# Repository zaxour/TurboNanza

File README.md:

# TurboNanza

***NOTE: I will provide support for Turbonanza if you purchased from:

My Ko-Fi Store: https://ko-fi.com/s/4d0de1c0ac
VideoGamePerfection (EU): https://videogameperfection.com/products/turbonanza-pcengine-turbografx/

If you purchased from AliExpress, I cannot provide support as it looks like they changed the design and did not publish the details.

***

[PC Engine Shuttle Installation Instructions](/images/shuttle/readme.md)

[PC Engine/Turbo Duo Installation Instructions](/images/duo/readme.md)

An internal RGB, S-Video, Composite video and Audio modification for the Turbografx 16, PCEngine and CoreGrafx. As of Revision C, support has been added for audio from the Turbo Everdrive Pro.

Design is KiCad format and all files necessary to open the design and have it fabricated are present within the archive.

Installation Method (WORK IN PROGRESS!!):

PINOUT (For reference/Non-Expansion-Port Installs):

## Step 1 - Remove the resistors for Luma, R-Y, B-Y, and Burst
### PC Engine & CoreGrafx

Remove resistors R134, R137, R138 and R156 

### TurboGrafx 16
Remove resistors R130-R132 and R134

### SuperGrafx
Remove resistors R164-167

## Step 2 - Disconnect CVBS pin from original circuit
### PC Engine & CoreGrafx
Remove resistor R145 (20 ohms)

### TurboGrafx 16
Remove resistor R127 (20 ohms)

### SuperGrafx
Remove resistor R147 

## Step 3 - Install TurboNanza
### PC Engine & CoreGrafx
Solder the TurboNanza over the expansion port pins as shown.

### TurboGrafx16
Solder the TurboNanza over the expansion port pins as shown.

### SuperGrafx
Prepare the flex cable by tinning the pads as shown.

Solder the TurboNanza to the flex cable as shown. It's recommended to verify continuity. Place some kapton/polyimide tape over the exposed solder pads on the bottom of the flex cable to avoid shorting to the shielding.

Solder the TurboNanza/Flex Cable combo over the expansion port pins as shown (ignore 4 wires at this time).

## Step 4 - Solder S-Video connections

**When soldering the Y/B-Y/R-Y/Burst wires, try to use as close to the exact same length of wire as possible to maintain proper phase shift!**

### PC Engine & CoreGrafx
Solder wires from the points shown to the pads on TurboNanza
(Do not remove R141, as previously directed. The Color Burst trace runs underneath and can easily sever. Leave R141 on and solder directly to the resistor pad)

### TurboGrafx 16
Solder wires from the points shown to the pads on TurboNanza

### SuperGrafx
Solder wires from the points shown to the pads on TurboNanza

## Step 5 - Attach the DIN to the main board
### PC Engine
Kits sold after 8/15/2023 now include a mounting board for the PCEngine. It is recommended to secure with two size M2 or 2-56 bolts/washers to allow for easy positioning.

Position the mount and loosely secure with screws/washers. The board may also be soldered - kapton/polyimide tape is recommended to position the board.

Place the DIN in the slot, and solder around the sides.

Solder the DIN FFC adapter to the DIN. Please make sure the "THIS SIDE TOP" text is visible before soldering, as it indicates which side is top.

### CoreGrafx
First, remove C162 (AC coupling capacitor for composite video - no longer necessary)

Scrape the solder mask off the copper on the left and right edges of the original DIN footprint as shown.

Solder the supplied mounting board to the mainboard.

Solder the DIN FFC adapter to the DIN. Please make sure the "THIS SIDE TOP" text is visible before soldering, as it indicates which side is top.

### TurboGrafx16
Solder the mounting board using the plated through holes for the RF modulator. Align the DIN on the mounting board such that it aligns with the console shell opening and solder in place.

### SuperGrafx
Remove the original DIN and scrape the soldermask approximately as shown.

Solder the mounting board as shown, aligning the center hole with the two ground through holes.

Mount the DIN and DIN board to the mount board.

## Step 6 - RF Shielding and Case trimming
### PC Engine
On the bottom shell of the case, trim the 2 ribs where the expansion port opening sits. Do not re-install the original shielding. If your PC Engine has shielding that has two tabs that solder close to the EXP port pins, you will need to run a wire to where the shielding originally terminated.

### CoreGrafx
Trim the RF shield such that the metal lip is not contacting the TurboNanza.

Like the PC Engine, trim the 2 ribs on the bottom shell where the expansion port opening is.

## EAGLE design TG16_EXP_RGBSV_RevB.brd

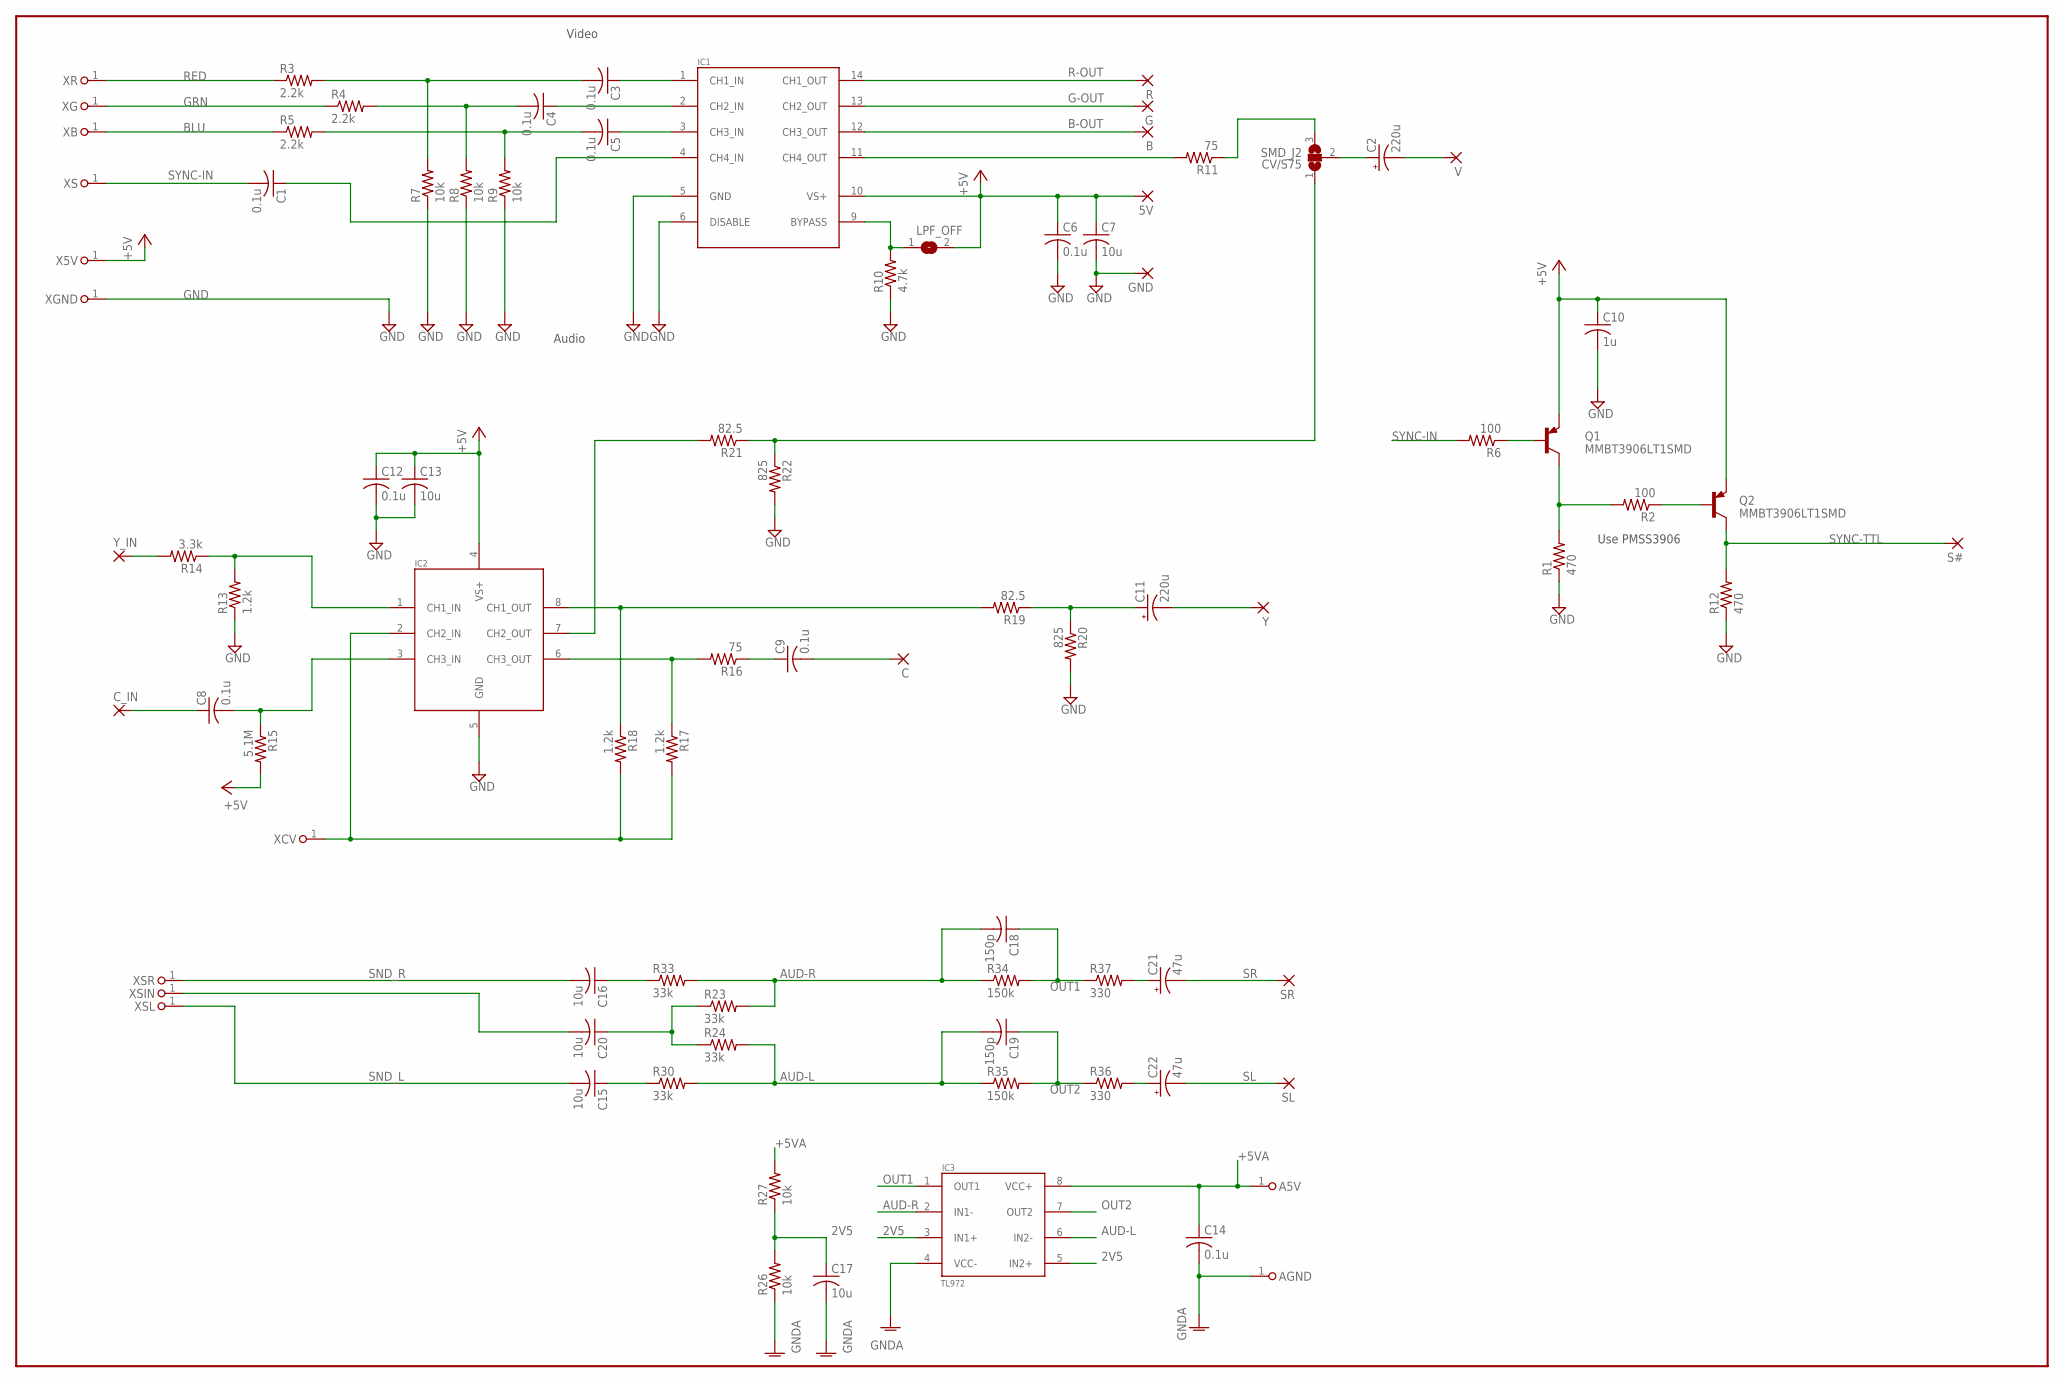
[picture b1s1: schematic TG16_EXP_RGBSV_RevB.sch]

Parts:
5V: SMD2; SMD1,27-2,54
A5V: PINHD-1X1; 1X01
AGND: PINHD-1X1; 1X01
B: SMD2; SMD1,27-2,54
C: SMD2; SMD1,27-2,54
C1, C3, C4, C5, C6, C8, C9, C12, C14: 0.1u; C0603
C2, C11: 220u; CT3528
C7, C13, C17: 10u; C1206
C10: 1u; C0603
C15, C16, C20: 10u; C0805
C18, C19: 150p; C0603
C21, C22: 47u; CT3528
CV/S75: SMD_J2; SJ_2
C_IN: SMD2; SMD1,27-2,54
G: SMD2; SMD1,27-2,54
GND: SMD2; SMD1,27-2,54
IC1: THS7374TSSOP14_LONG; TSSOP14LONG
IC2: THS7314; SOIC8
IC3: TL972; SOIC8
LPF_OFF: SMD_J; SJ
Q1, Q2: MMBT3906LT1SMD; SOT23-BEC
R: SMD2; SMD1,27-2,54
R1, R12: 470; R0603
R2, R6: 100; R0603
R3, R4, R5: 2.2k; R0603
R7, R8, R9, R26, R27: 10k; R0603
R10: 4.7k; R0603
R11, R16: 75; R0603
R13, R17, R18: 1.2k; R0603
R14: 3.3k; R0603
R15: 5.1M; R0603
R19, R21: 82.5; R0603
R20, R22: 825; R0603
R23, R24, R30, R33: 33k; R0603
R34, R35: 150k; R0603
R36, R37: 330; R0603
S#: SMD2; SMD1,27-2,54
SL: SMD2; SMD1,27-2,54
SR: SMD2; SMD1,27-2,54
V: SMD2; SMD1,27-2,54
X5V: PINHD-1X1; 1X01
XB: PINHD-1X1; 1X01
XCV: PINHD-1X1; 1X01
XG: PINHD-1X1; 1X01
XGND: PINHD-1X1; 1X01
XR: PINHD-1X1; 1X01
XS: PINHD-1X1; 1X01
XSIN: PINHD-1X1; 1X01
XSL: PINHD-1X1; 1X01
XSR: PINHD-1X1; 1X01
Y: SMD2; SMD1,27-2,54
Y_IN: SMD2; SMD1,27-2,54

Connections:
2V5: C17.1, IC3.3 (IN1+), IC3.5 (IN2+), R26.2, R27.1
+5V: 5V.1, C6.1, C7.1, C10.1, C12.1, C13.1, IC1.10 (VS+), IC2.4 (VS+), LPF_OFF.2, Q1.E, Q2.E, R15.2, X5V.1
+5VA: A5V.1, C14.1, IC3.8 (VCC+), R27.2
AUD-L: C19.2, IC3.6 (IN2-), R24.2, R30.2, R35.1
AUD-R: C18.2, IC3.2 (IN1-), R23.2, R33.2, R34.1
B-OUT: B.1, IC1.12 (CH3_OUT)
BLU: R5.1, XB.1
G-OUT: G.1, IC1.13 (CH2_OUT)
GND: C6.2, C7.2, C10.2, C12.2, C13.2, GND.1, IC1.5 (GND), IC1.6 (DISABLE), IC2.5 (GND), R1.1, R7.1, R8.1, R9.1, R10.1, R12.1, R13.1, R20.2, R22.2, XGND.1
GNDA: AGND.1, C14.2, C17.2, IC3.4 (VCC-), R26.1
GRN: R4.1, XG.1
unnamed: Q1.B, R6.1
unnamed: C3.1, IC1.1 (CH1_IN)
unnamed: C3.2, R3.2, R7.2
unnamed: C4.1, IC1.2 (CH2_IN)
unnamed: C4.2, R4.2, R8.2
unnamed: C5.1, IC1.3 (CH3_IN)
unnamed: C1.1, IC1.4 (CH4_IN)
unnamed: C5.2, R5.2, R9.2
unnamed: IC1.9 (BYPASS), LPF_OFF.1, R10.2
unnamed: Q1.C, R1.2, R2.2
unnamed: IC1.11 (CH4_OUT), R11.2
unnamed: Q2.B, R2.1
unnamed: C2.+, CV/S75.2
unnamed: C2.-, V.1
unnamed: R14.2, Y_IN.1
unnamed: IC2.1 (CH1_IN), R13.2, R14.1
unnamed: C8.1, C_IN.1
unnamed: C8.2, IC2.3 (CH3_IN), R15.1
unnamed: IC2.8 (CH1_OUT), R18.1, R19.2
unnamed: IC2.6 (CH3_OUT), R16.2, R17.1
unnamed: C9.1, R16.1
unnamed: C.1, C9.2
unnamed: IC2.2 (CH2_IN), R17.2, R18.2, XCV.1
unnamed: C11.+, R19.1, R20.1
unnamed: C11.-, Y.1
unnamed: IC2.7 (CH2_OUT), R21.2
unnamed: CV/S75.3, R11.1
unnamed: CV/S75.1, R21.1, R22.1
unnamed: C16.1, R33.1
unnamed: C20.2, XSIN.1
unnamed: C20.1, R23.1, R24.1
unnamed: C15.1, R30.1
unnamed: C22.+, R36.2
unnamed: C21.+, R37.2
OUT1: C18.1, IC3.1 (OUT1), R34.2, R37.1
OUT2: C19.1, IC3.7 (OUT2), R35.2, R36.1
R-OUT: IC1.14 (CH1_OUT), R.1
RED: R3.1, XR.1
SL: C22.-, SL.1
SND_L: C15.2, XSL.1
SND_R: C16.2, XSR.1
SR: C21.-, SR.1
SYNC-IN: C1.2, R6.2, XS.1
SYNC-TTL: Q2.C, R12.2, S#.1

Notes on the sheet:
Audio
Video
Use PMSS3906

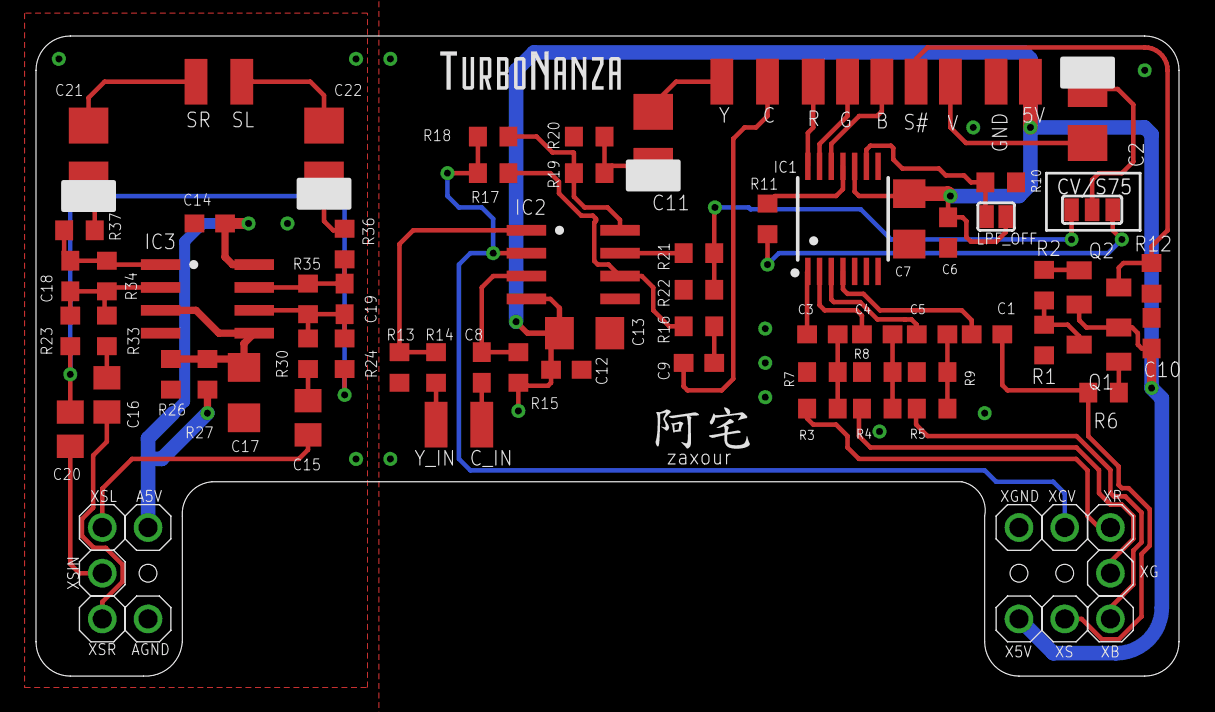
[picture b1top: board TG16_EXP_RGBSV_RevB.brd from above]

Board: 2 copper layers, 63.5 x 35.6 mm, 86 parts (0 on the bottom side), 55 nets.

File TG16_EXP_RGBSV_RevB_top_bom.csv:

Comment,Designator,Footprint,LCSC Part #
0.1u,C1 C3 C4 C5 C6 C8 C9 C12 C14,C0603,
1.2k,R13 R17 R18,R0603,
1u,C10,C0603,
2.2k,R3 R4 R5,R0603,
3.3k,R14,R0603,
4.7k,R10,R0603,
5.1M,R15,R0603,
10k,R7 R8 R9 R26 R27,R0603,
10u,C7 C13,C1206,
10u,C15 C16,C0805,
10u,C17,C1206,
10u,C20,C0805,
33k,R23 R24 R30 R33,R0603,
47u,C21 C22,CT3528,
75,R11 R16,R0603,
82.5,R19 R21,R0603,
100,R2 R6,R0603,
150k,R34 R35,R0603,
150p,C18 C19,C0603,
220u,C2 C11,CT3528,
330,R36 R37,R0603,
470,R1 R12,R0603,
825,R20 R22,R0603,
MMBT3906LT1SMD,Q1 Q2,SOT23-BEC,
SMD_J,LPF_OFF,SJ,
SMD_J2,CV/S75,SJ_2,
THS7314,IC2,SOIC8,
THS7374TSSOP14_LONG,IC1,TSSOP14LONG,
TL972,IC3,SOIC8,

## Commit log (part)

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2022-09-25 Add files via upload
    Replaced Eagle version with revised KiCad version
2023-02-17 Update README.md
    Updated with PC Engine Steps
2023-05-09 Update README.md
    Added admonishment about R141 on PCE/CG systems.
2023-05-12 Create LICENSE
2023-06-25 Update README.md
    Additional CoreGrafx handling instructions.
2023-08-15 Add files via upload
    PC Engine mounting board added
2023-08-28 Create readme.md
    Initial Duo instructions draft
2024-09-21 Update readme.md
    Forgot about resistor removal; not critical, but suggested to do so.
2025-04-20 Update README.md
    Updated PCE/CG Step 4 photo for clarity
2025-09-28 Update README.md
    Updated DIN mounting instructions for PCE/CG
2025-09-28 Update readme.md
    Updated Duo DIN and Audio instructions
